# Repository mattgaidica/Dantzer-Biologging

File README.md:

# What is bio-logging?
The use of miniaturized, animal-borne bio-loggers to make physiological and environmental measurements from free-ranging animals is radically transforming scientific capabilities ([Williams et al., 2019](https://besjournals.onlinelibrary.wiley.com/doi/abs/10.1111/1365-2656.13094)). We have recently explored how to implement these technologies to expand the methods and resolution by which stress and performance are quantified in the wild ([Gaidica & Dantzer, 2019](https://ecoevorxiv.org/huxw6/)).

### Current Challenges
Bio-logging is historically niche due to the unique constraints of field biologists. From fish to birds, it is unreasonable to expect a one-size-fits-all solution. However, the ambitious goals of individuals *can and should* generalize to the bio-logging community under the following headings:

1. _Standardize_ data collection and analysis methods.
2. _Communicate_ approaches and insights.
3. _Innovate_ tools and technologies.

We are doing our best to make our projects **open source**. You can read more about our approach in [the Wiki](https://github.com/mattgaidica/biologging/wiki/Architecture).

## Why squirrels?

The ecological niche occupied by wild squirrels has been conserved for millions of years and is highlighted by their unique adaptations to arboreal life (i.e., in the trees). Their ability to regulate energy and maintain fitness through a variety of natural and imposed challenges ultimately determine their pedigree and survival. Little is known about how the central nervous system (CNS) is involved in these natural behaviors. One of our goals is to use bio-loggers to record from the CNS of wild squirrels to understand how their physiology and behavior are correlated, given the varying demands of their environment. Adding resolution to these important ecological factors is an important consideration to ongoing conservation work, potentially highlighting what ‘optimal adaptations’ are from a physiological perspective.

### Research Platform

Evolutionary pressures on wild animals engender advantageous platforms for study because behavior is so crucially linked with fitness. How mammalian physiology copes and adapts in response to changing environments is an important question that can benefit from the added resolution of bio-loggers. In addition to scientific investigations, the squirrel is a useful model to address many outstanding technical challenges—not unique to ecology—that make long-duration studies in harsh environments possible.

### Kluane Red Squirrel Project
[The Kluane Red Squirrel Project](https://redsquirrel.biology.ualberta.ca) (KRSP) is an interdisciplinary, large-scale field experiment located in the Canadian Yukon. KRSP has been collecting ecological and behavioral data on squirrels since 1987 and conducts a variety of studies and surveys on the population and food availability every year.

Squirrels in the Yukon face intense challenges including drastic changes in light/dark cycles through each season. During the summer months there is very little darkness (see image above). This natural rhythm makes KRSP and the squirrel an ideal candidate to study the affects of circadian entrainment.

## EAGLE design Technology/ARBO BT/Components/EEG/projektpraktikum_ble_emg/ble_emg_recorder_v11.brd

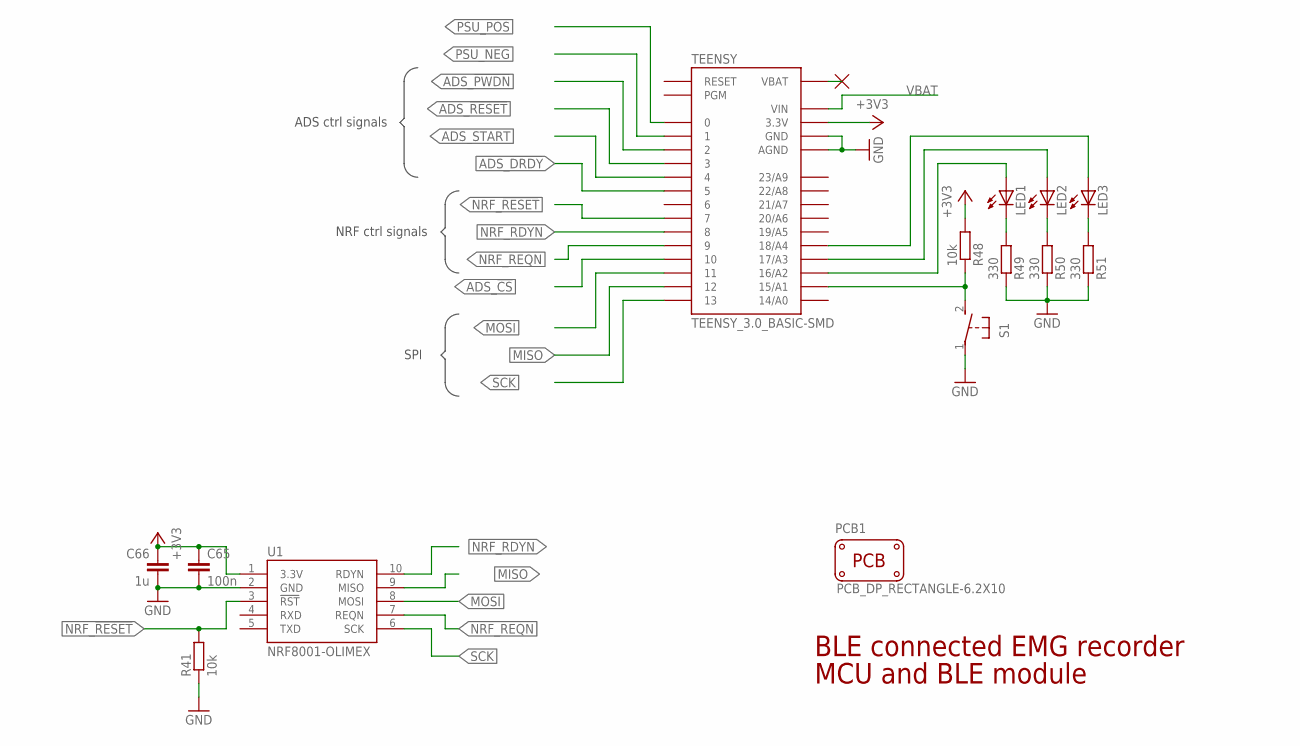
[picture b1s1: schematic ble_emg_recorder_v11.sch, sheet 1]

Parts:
C65: 100n; C0805; DIGIKEY 1276-1099-1-ND
C66: 1u; C0805; DIGIKEY 1276-1066-1-ND
LED1, LED2, LED3: LEDCHIPLED_0805; CHIPLED_0805
PCB1: PCB_DP_RECTANGLE-6.2X10; DP10062_V1
R41, R48: 10k; R0805
R49, R50, R51: 330; R0805; DIGIKEY RMCF0805JT330RCT-ND
S1: 31-XX; B3F-31XX
TEENSY: TEENSY_3.0_BASIC-SMD
U1: NRF8001-OLIMEX

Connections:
+3V3: C65.1, C66.1, R48.2, TEENSY.3.3V, TEENSY.3.3V1 (3.3V), U1.1 (3.3V); also elsewhere on the board
ADS_!CS: TEENSY.10; also elsewhere on the board
ADS_!DRDY: TEENSY.5; also elsewhere on the board
ADS_!PWDN: TEENSY.2; also elsewhere on the board
ADS_!RESET: TEENSY.3; also elsewhere on the board
ADS_START: TEENSY.4; also elsewhere on the board
GND: C65.2, C66.2, R41.1, R49.1, R50.1, R51.1, S1.1, TEENSY.AGND, TEENSY.GND, TEENSY.GND1 (GND), U1.2 (GND); also elsewhere on the board
MISO: TEENSY.12, U1.9 (MISO); also elsewhere on the board
MOSI: TEENSY.11, U1.8 (MOSI); also elsewhere on the board
unnamed: R48.1, S1.2 (S), TEENSY.15/A1
unnamed: LED1.A, TEENSY.16/A2
unnamed: LED2.A, TEENSY.17/A3
unnamed: LED3.A, TEENSY.18/A4
unnamed: LED1.C, R49.2
unnamed: LED2.C, R50.2
unnamed: LED3.C, R51.2
NRF_!RESET: R41.2, TEENSY.7, U1.3 (!RST)
NRF_RDYN: TEENSY.8, U1.10 (RDYN)
NRF_REQN: TEENSY.9, U1.7 (REQN)
PSU_NEG: TEENSY.1; also elsewhere on the board
PSU_POS: TEENSY.0; also elsewhere on the board
SCK: TEENSY.13, U1.6 (SCK); also elsewhere on the board
VBAT: TEENSY.VIN; also elsewhere on the board

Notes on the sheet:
ADS ctrl signals
NRF ctrl signals
SPI
BLE connected EMG recorder
MCU and BLE module

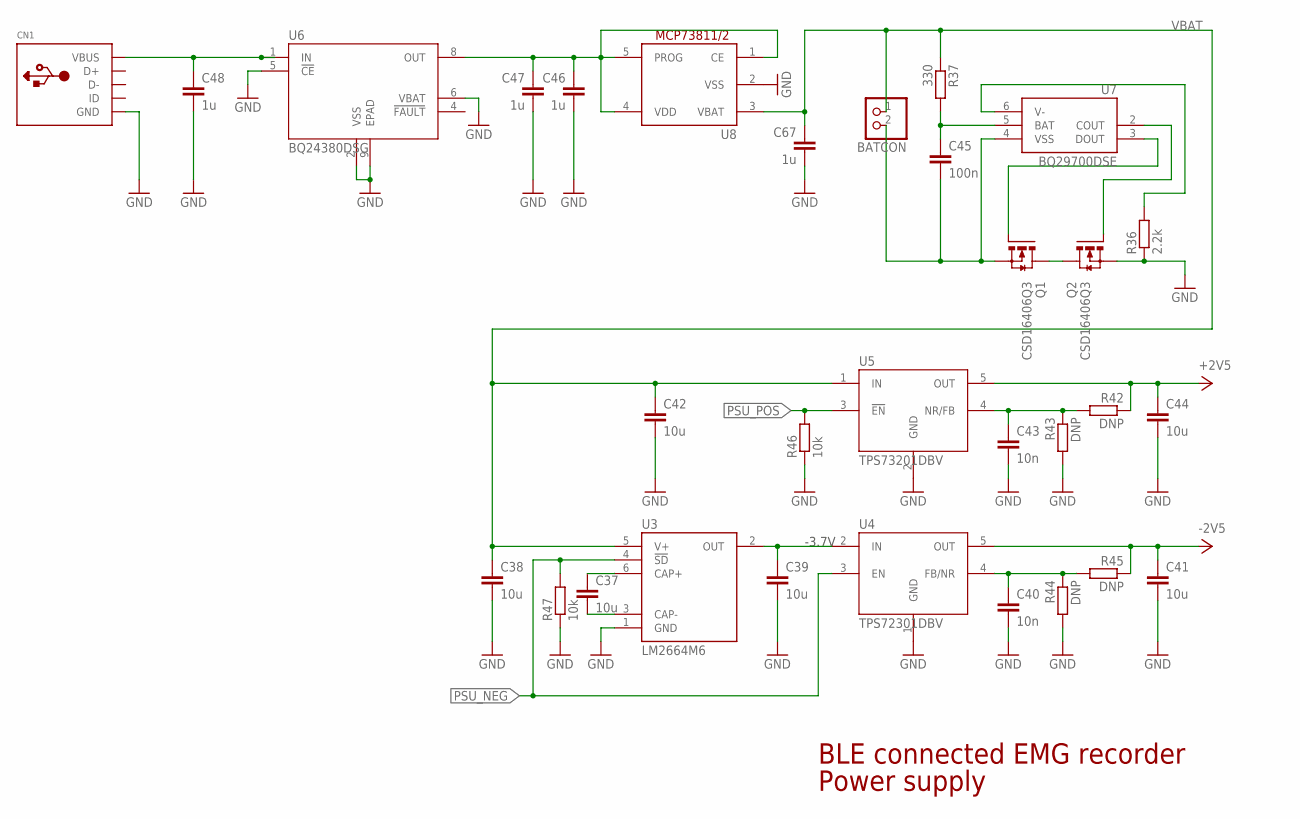
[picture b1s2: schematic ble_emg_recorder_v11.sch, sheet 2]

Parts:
BATCON: JST_2PIN-THM-RA; JST-PH-2-THM-RA; DIGIKEY 455-1719-ND
C37, C38, C39, C41, C42, C44: 10u; C0805; DIGIKEY 1276-2891-1-ND
C40, C43: 10n; C0805; DIGIKEY 1276-1015-1-ND
C45: 100n; C0805; DIGIKEY 1276-1099-1-ND
C46, C47, C48, C67: 1u; C0805; DIGIKEY 1276-1066-1-ND
CN1: USBMINIB; USB-MINIB; DIGIKEY ED2992CT-ND
Q1, Q2: CSD16406Q3; DQV8-L; DIGIKEY 296-24251-1-ND
R36: 2.2k; R0805; DIGIKEY RMCF0805JT2K20CT-ND
R37: 330; R0805; DIGIKEY RMCF0805JT330RCT-ND
R42, R43, R44, R45: DNP; R0805
R46, R47: 10k; R0805
U3: LM2664M6; SOT95P300X120-6N; DIGIKEY LM2664M6CT-ND
U4: TPS72301DBV; DBV5; DIGIKEY 296-15799-1-ND
U5: TPS73201DBV; DBV5; DIGIKEY 296-15810-1-ND
U6: BQ24380DSG; DSG8_P9X1P6; DIGIKEY 296-23385-1-ND
U7: BQ29700DSE; DSE6; DIGIKEY 296-37746-1-ND
U8: MCP73811/2; SOT23-5L; DIGIKEY MCP73811T-420I/OTCT-ND

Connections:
+2V5: C44.1, R42.1, U5.5 (OUT); also elsewhere on the board
-2V5: C41.1, R45.1, U4.5 (OUT); also elsewhere on the board
GND: C38.2, C39.2, C40.2, C41.2, C42.2, C43.2, C44.2, C46.2, C47.2, C48.2, C67.2, CN1.GND, Q2.1 (S), Q2.2 (S), Q2.3 (S), R36.1, R43.2, R44.2, R46.1, R47.1, U3.1 (GND), U4.1 (GND), U5.2 (GND), U6.2 (VSS), U6.5 (!CE), U6.6 (VBAT), U6.9 (EPAD), U8.2 (VSS); also elsewhere on the board
unnamed: C40.1, R44.1, R45.2, U4.4 (FB/NR)
unnamed: C46.1, C47.1, U6.8 (OUT), U8.1 (CE), U8.4 (VDD), U8.5 (PROG)
unnamed: C37.1, U3.6 (CAP+)
unnamed: C37.2, U3.3 (CAP-)
unnamed: C39.1, U3.2 (OUT), U4.2 (IN)
unnamed: C43.1, R42.2, R43.1, U5.4 (NR/FB)
unnamed: BATCON.2 (1), C45.2, Q1.1 (S), Q1.2 (S), Q1.3 (S), U7.4 (VSS)
unnamed: Q2.4 (G), U7.2 (COUT)
unnamed: Q1.4 (G), U7.3 (DOUT)
unnamed: R36.2, U7.6 (V-)
unnamed: C45.1, R37.2, U7.5 (BAT)
unnamed: Q1.5 (D), Q1.6 (D), Q1.7 (D), Q1.8 (D), Q2.5 (D), Q2.6 (D), Q2.7 (D), Q2.8 (D)
PSU_NEG: R47.2, U3.4 (!SD), U4.3 (EN); also elsewhere on the board
PSU_POS: R46.2, U5.3 (!EN); also elsewhere on the board
VAC: C48.1, CN1.VBUS, U6.1 (IN)
VBAT: BATCON.1 (2), C38.1, C42.1, C67.1, R37.1, U3.5 (V+), U5.1 (IN), U8.3 (VBAT); also elsewhere on the board

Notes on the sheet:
-3.7V
BLE connected EMG recorder
Power supply

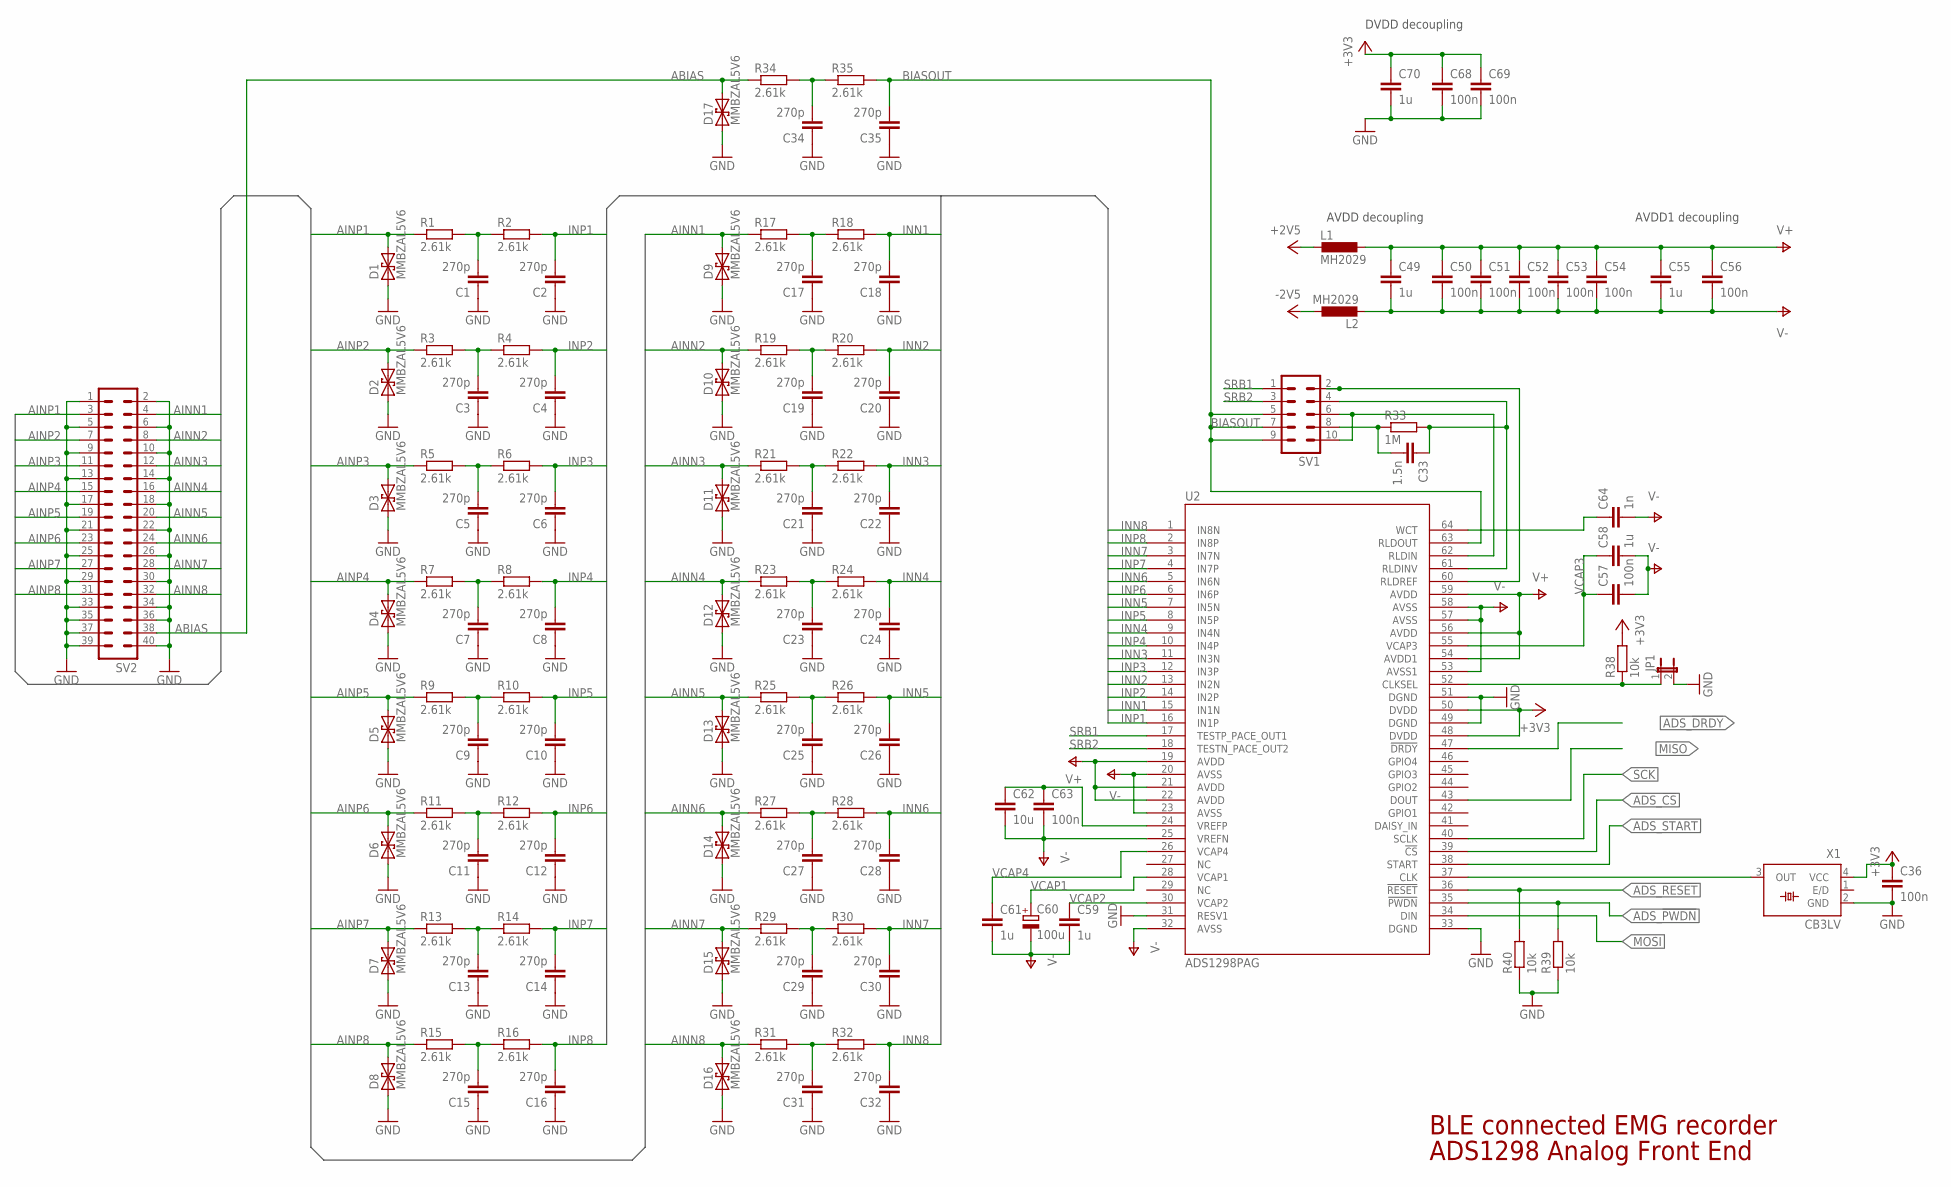
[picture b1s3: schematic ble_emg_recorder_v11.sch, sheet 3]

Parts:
C1, C2, C3, C4, C5, C6, C7, C8, C9, C10, C11, C12, C13, C14, C15, C16, C17, C18, C19, C20, C21, C22, C23, C24, C25, C26, C27, C28, C29, C30, C31, C32, C34, C35: 270p; C0805; DIGIKEY 1276-2494-1-ND
C33: 1.5n; C0805; DIGIKEY 1276-1794-1-ND
C36: 100n; C0805; DIGIKEY 1276-1099-1-ND
C49, C55, C58, C59, C61, C70: 1u; C0805; DIGIKEY 1276-1066-1-ND
C50, C51, C52, C53, C54, C56, C57, C63, C68, C69: 100n; C0402; DIGIKEY 1276-1443-1-ND
C60: 100u; D/7343-31W; DIGIKEY 399-3772-1-ND
C62: 10u; C0805; DIGIKEY 1276-2891-1-ND
C64: 1n; C0402; DIGIKEY 311-1036-1-ND
D1, D2, D3, D4, D5, D6, D7, D8, D9, D10, D11, D12, D13, D14, D15, D16, D17: MMBZAL5V6; SOT23; DIGIKEY 568-6347-1-ND
JP1: JP1E; JP1
L1, L2: MH2029; L0805; DIGIKEY MH2029-221YCT-ND
R1, R2, R3, R4, R5, R6, R7, R8, R9, R10, R11, R12, R13, R14, R15, R16, R17, R18, R19, R20, R21, R22, R23, R24, R25, R26, R27, R28, R29, R30, R31, R32, R34, R35: 2.61k; R0805; DIGIKEY RMCF0805FT2K61CT-ND
R33: 1M; R0805; DIGIKEY RMCF0805JT1M00CT-ND
R38, R39, R40: 10k; R0805
SV1: MA05-2
SV2: ML40; DIGIKEY S9175-ND
U2: ADS1298PAG; PAG64; DIGIKEY 296-27734-ND
X1: CB3LV; SM77H; DIGIKEY CTX1277CT-ND

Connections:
+2V5: L1.2; also elsewhere on the board
+3V3: C36.1, C68.1, C69.1, C70.1, R38.2, U2.48 (DVDD), U2.50 (DVDD), X1.4 (VCC); also elsewhere on the board
-2V5: L2.1; also elsewhere on the board
ABIAS: D17.2, R34.1, SV2.38
ADS_!CS: U2.39 (!CS); also elsewhere on the board
ADS_!DRDY: U2.47 (!DRDY); also elsewhere on the board
ADS_!PWDN: R39.2, U2.35 (!PWDN); also elsewhere on the board
ADS_!RESET: R40.2, U2.36 (!RESET); also elsewhere on the board
ADS_CLK: U2.37 (CLK), X1.3 (OUT)
ADS_START: U2.38 (START); also elsewhere on the board
AINN1: D9.2, R17.1, SV2.4
AINN2: D10.2, R19.1, SV2.8
AINN3: D11.2, R21.1, SV2.12
AINN4: D12.2, R23.1, SV2.16
AINN5: D13.2, R25.1, SV2.20
AINN6: D14.2, R27.1, SV2.24
AINN7: D15.2, R29.1, SV2.28
AINN8: D16.2, R31.1, SV2.32
AINP1: D1.2, R1.1, SV2.3
AINP2: D2.2, R3.1, SV2.7
AINP3: D3.2, R5.1, SV2.11
AINP4: D4.2, R7.1, SV2.15
AINP5: D5.2, R9.1, SV2.19
AINP6: D6.2, R11.1, SV2.23
AINP7: D7.2, R13.1, SV2.27
AINP8: D8.2, R15.1, SV2.31
BIASOUT: C35.2, R35.2, SV1.5, SV1.7, SV1.9, U2.63 (RLDOUT)
GND: C1.1, C2.1, C3.1, C4.1, C5.1, C6.1, C7.1, C8.1, C9.1, C10.1, C11.1, C12.1, C13.1, C14.1, C15.1, C16.1, C17.1, C18.1, C19.1, C20.1, C21.1, C22.1, C23.1, C24.1, C25.1, C26.1, C27.1, C28.1, C29.1, C30.1, C31.1, C32.1, C34.1, C35.1, C36.2, C68.2, C69.2, C70.2, D1.1, D2.1, D3.1, D4.1, D5.1, D6.1, D7.1, D8.1, D9.1, D10.1, D11.1, D12.1, D13.1, D14.1, D15.1, D16.1, D17.1, JP1.2, R39.1, R40.1, SV2.1, SV2.2, SV2.5, SV2.6, SV2.9, SV2.10, SV2.13, SV2.14, SV2.17, SV2.18, SV2.21, SV2.22, SV2.25, SV2.26, SV2.29, SV2.30, SV2.33, SV2.34, SV2.35, SV2.36, SV2.37, SV2.39, SV2.40, U2.31 (RESV1), U2.33 (DGND), U2.49 (DGND), U2.51 (DGND), X1.2 (GND); also elsewhere on the board
INN1: C18.2, R18.2, U2.15 (IN1N)
INN2: C20.2, R20.2, U2.13 (IN2N)
INN3: C22.2, R22.2, U2.11 (IN3N)
INN4: C24.2, R24.2, U2.9 (IN4N)
INN5: C26.2, R26.2, U2.7 (IN5N)
INN6: C28.2, R28.2, U2.5 (IN6N)
INN7: C30.2, R30.2, U2.3 (IN7N)
INN8: C32.2, R32.2, U2.1 (IN8N)
INP1: C2.2, R2.2, U2.16 (IN1P)
INP2: C4.2, R4.2, U2.14 (IN2P)
INP3: C6.2, R6.2, U2.12 (IN3P)
INP4: C8.2, R8.2, U2.10 (IN4P)
INP5: C10.2, R10.2, U2.8 (IN5P)
INP6: C12.2, R12.2, U2.6 (IN6P)
INP7: C14.2, R14.2, U2.4 (IN7P)
INP8: C16.2, R16.2, U2.2 (IN8P)
MISO: U2.43 (DOUT); also elsewhere on the board
MOSI: U2.34 (DIN); also elsewhere on the board
unnamed: C1.2, R1.2, R2.1
unnamed: C3.2, R3.2, R4.1
unnamed: C34.2, R34.2, R35.1
unnamed: C5.2, R5.2, R6.1
unnamed: C7.2, R7.2, R8.1
unnamed: SV1.6, SV1.10, U2.62 (RLDIN)
unnamed: C9.2, R9.2, R10.1
unnamed: C33.2, R33.1, SV1.8
unnamed: C11.2, R11.2, R12.1
unnamed: C33.1, R33.2, SV1.4, U2.61 (RLDINV)
unnamed: C13.2, R13.2, R14.1
unnamed: C15.2, R15.2, R16.1
unnamed: SV1.2, U2.60 (RLDREF)
unnamed: C17.2, R17.2, R18.1
unnamed: C19.2, R19.2, R20.1
unnamed: C21.2, R21.2, R22.1
unnamed: C23.2, R23.2, R24.1
unnamed: C25.2, R25.2, R26.1
unnamed: C27.2, R27.2, R28.1
unnamed: C29.2, R29.2, R30.1
unnamed: C31.2, R31.2, R32.1
unnamed: JP1.1, R38.1, U2.52 (CLKSEL)
unnamed: C64.1, U2.64 (WCT)
SCK: U2.40 (SCLK); also elsewhere on the board
SRB1: SV1.1, U2.17 (TESTP_PACE_OUT1)
SRB2: SV1.3, U2.18 (TESTN_PACE_OUT2)
V+: C49.1, C50.1, C51.1, C52.1, C53.1, C54.1, C55.1, C56.1, L1.1, U2.19 (AVDD), U2.21 (AVDD), U2.22 (AVDD), U2.54 (AVDD1), U2.56 (AVDD), U2.59 (AVDD)
V-: C49.2, C50.2, C51.2, C52.2, C53.2, C54.2, C55.2, C56.2, C57.2, C58.2, C59.2, C60.-, C61.2, C62.2, C63.2, C64.2, L2.2, U2.20 (AVSS), U2.23 (AVSS), U2.25 (VREFN), U2.32 (AVSS), U2.53 (AVSS1), U2.57 (AVSS), U2.58 (AVSS)
VCAP1: C60.+, U2.28 (VCAP1)
VCAP2: C59.1, U2.30 (VCAP2)
VCAP3: C57.1, C58.1, U2.55 (VCAP3)
VCAP4: C61.1, U2.26 (VCAP4)
VREFP: C62.1, C63.1, U2.24 (VREFP)

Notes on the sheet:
AVDD decoupling
AVDD1 decoupling
BLE connected EMG recorder
ADS1298 Analog Front End
DVDD decoupling

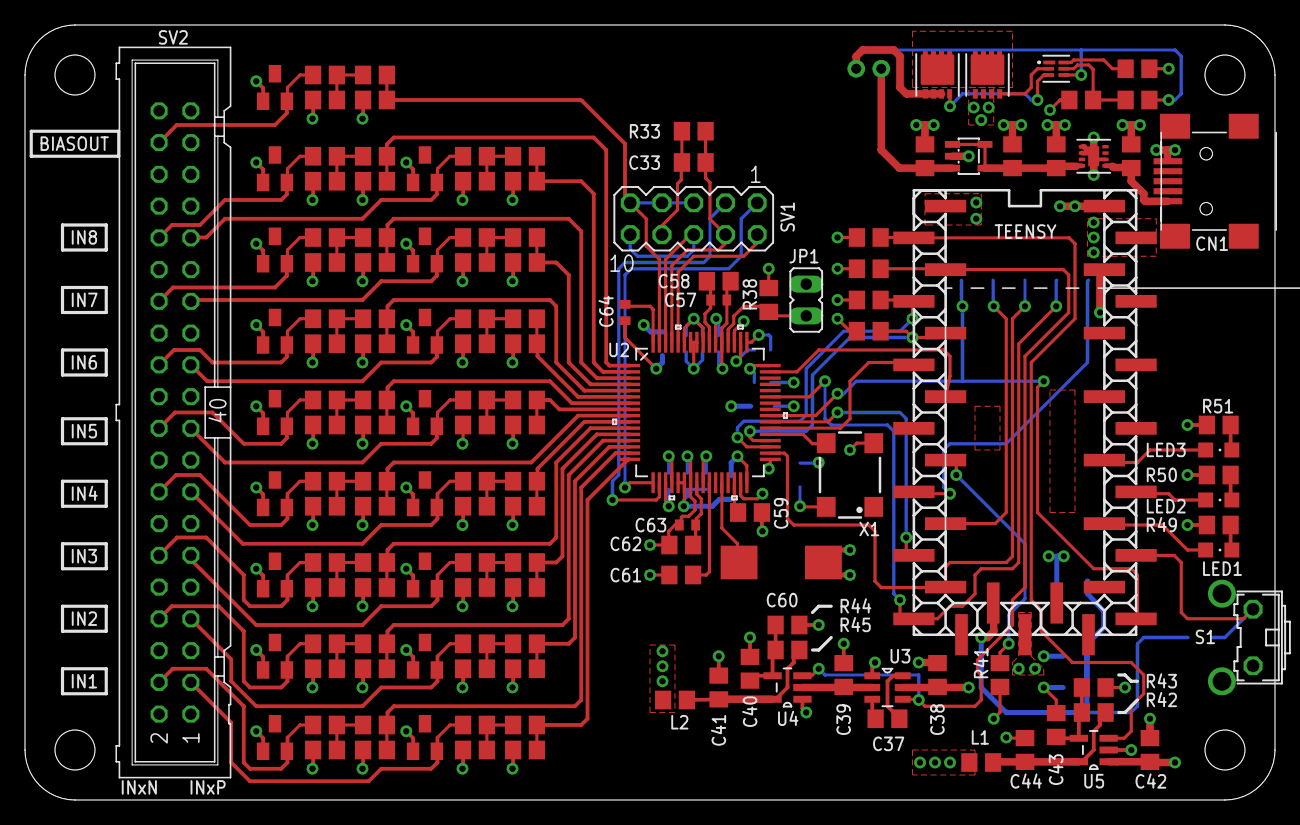
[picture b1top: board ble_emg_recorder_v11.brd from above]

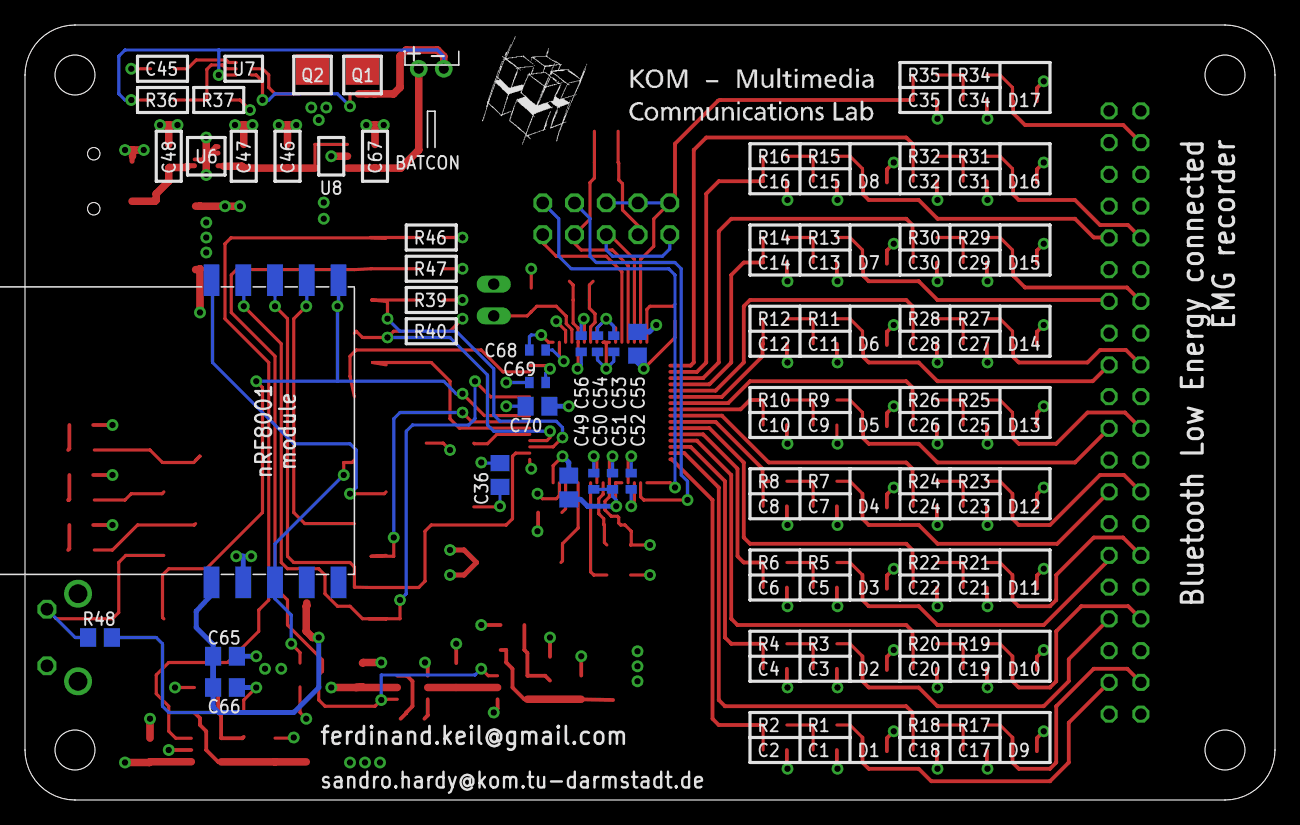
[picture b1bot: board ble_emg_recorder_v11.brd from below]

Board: 8 copper layers, 100.0 x 62.0 mm, 163 parts (18 on the bottom side), 105 nets.

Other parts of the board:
U$5: KOM_LOGO

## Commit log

2019-12-05 Set theme jekyll-theme-minimal
2019-12-05 add gitignore
2019-12-05 Including Testbed design
2019-12-05 Including KiCad
2019-12-06 Create CNAME
2019-12-06 Update CNAME
2019-12-06 change theme
2019-12-06 update theme
2019-12-06 logo
2019-12-06 updating layout
2019-12-06 changed logo size
2019-12-06 added css for future
2019-12-06 updated logo
2019-12-06 homepage
2019-12-06 squirrels
2019-12-06 smaller
2019-12-06 adjust footer
2019-12-06 borders
2019-12-07 css ext
2019-12-07 adding testbed
2019-12-07 new logo
2019-12-09 squirrel platform
2019-12-10 show light dark
2019-12-14 Wiki QR code
2019-12-21 Updated testbed
2020-01-06 Updating values to match changes on board
2020-01-07 ARBO Mini hackathon
2020-01-08 Exported gerbers
2020-01-09 ARBO mini sent to JSTPCB for fab
2020-01-23 ARBO mini FRAM pads are backwards, fix later
2020-03-04 Changing RF design for BT
2020-04-01 Added ARBO BT and NUTS
2020-04-03 Got Nuts PCB prototype working, needs updates
2020-07-27 Working on pink noise
2020-08-12 Working on ESLO
2020-08-16 Making progress on ESLO
2020-08-18 Added ESLO
2020-08-21 ESLO changelog
2020-08-21 rm changelog
2020-08-25 Added ESLO debugger and PSP
2020-08-28 ESLO project updates
2020-09-02 Reconsidering ESLO architecture (-> CC2640R2)
2020-09-03 Datasheets
2020-09-03 allow all assets
2020-09-16 new RF footprints
2020-09-18 ESLO RB
2020-09-23 Redo ESLO_RB with AC coupling
2020-09-24 Completed RB design
2020-09-24 Checked all pins, ready for production
2020-09-28 Submit ESLO_RB for mfg w PCBONLINE
2020-10-04 Debugger submitted
2020-10-21 Assembling ESLO_RB
2020-10-27 ESLO Updates
2020-10-31 Debugging ESLO PBCs
2020-11-05 Debugging
2020-11-08 Cleaning
2020-11-10 Submitted ESLO_RB for TI hardware review
2020-11-17 Weblocs
2020-11-29 Added BTE docs
2020-12-01 Notes
2020-12-08 Added notes
2020-12-15 rm ds_store
2021-01-19 NAND updates
2021-02-17 Updated note on ESLO_RB
2021-02-20 kicad
2021-02-22 New thermistor datasheets
2021-02-23 Seeking LSM303AGR
2021-05-14 ESLO RB2
2021-05-26 ESLO Parts
2021-06-08 Adding all schematics/layouts/tech projects
2021-06-29 Schematics
2021-07-12 Comments
2021-07-28 Update schematics
